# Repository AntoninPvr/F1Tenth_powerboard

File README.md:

# F1Tenth power board

This repository contains the power board design for a F1Tenth car.

Designed on Kicad 9.0.6.

## History
This project was originally launched in the summer of 2024 at [CTU](https://www.cvut.cz/en), thanks to David Zahrádka, to facilitate easier experimentation for researchers.

## Assembled PCB

## Features

This board is designed to power all F1tenth components. Two 3S Li-Po batteries power the board. Those batteries are connected in parallel throught an ORing circuitry. This allow to hot swap batteries. The output of the ORing is named `BATT_SYS` and is directly connected to VESC output **without protections**.

The `Jetson` terminals is also connected to `BATT_SYS` but protected by a dedicated 5A e-fuse. The `P_0` and `P_1` terminals are connected to `BATT_SYS` through another e-fuse and can draw up to 5A.

A 5V 6A buck converter provide power to the `USB A` connector. This output is protected for overcurrent up to 6A.

## SAFETY WARNING

Li-Po can provide **huge amount** of current. **Be careful** when handling the board. **Do not short circuit** the batteries and VESC output as they are not protected. Do not exceed the maximum input voltage: **20V**.

PCB can be hot when drawing high current. 

## Absolute maximum ratings
| | Min | Max | Unit
--- | --- | --- | ---
Battery voltage | 6 | 20 | V
Jetson current |  | 5 | A
P0 + P1 current |  | 5 | A
USB current |  | 6 | A
VESC current |  | 60 | A

## File structure

- [power_board.pro](power_board_f1tenth.kicad_pro) - Kicad project file
- [power_board.sch](power_board_f1tenth.kicad_sch) - Schematic
- [power_board.kicad_pcb](power_board_f1tenth.kicad_pcb) - PCB layout
- [symbol/](symbol/) - Custom symbols
- [power_board.pretty/](symbol/) - Custom footprints

## DRC

Design rules checks comply with JLCPCB capabilities.

## Circuit

### Ideal diode

Ideal diode behavior is achieved by LM74700 and the high power N channel MOSFET IAUCN04S7L005.

The `J3` can be used to connect a battery life indicator.

Circuit for battery B is identical.

### Buck converter

Provide 5V 6A to the USB connector. Data p and n are tied together as the USB connector is only used for power, it helps to trigger high current mode on some device.

TPS51386 also provide overcurrent protection, under and overvoltage protection.

### E-fuse

Those e-fuse are used to protect the Jetson and the peripherals. The TPS25980 is configured to limit the current to 5A. It allow overcurrrent for 2ms to allow inrush current. Number of retry is unlimited and rise time is 1ms.

### Terminals

Terminal are bornier-2_P5.08mm. They are used to connect the peripherals and the Jetson. They are from the MSTB series from Phoenix Contact. They can be easily unpluged and pluged.

## PCB

## BOM
Designator | Footprint | Quantity | Value
--- | --- | --- | ---
C1, C14, C15, C18, C2, C5, C6, C7, C8 | 0805 | 9 | 22u
C10 | 0805 | 1 | 22p
C11 | 0805 | 1 | NC
C12, C13, C16, C21, C3, C4 | 0805 | 6 | 100n
C17, C19, C20, C22, C23, C24 | 0805 | 6 | 10n
C9 | 0805 | 1 | 1u
D1 | SOT96P237X111-3N | 1 | 3.3v
D2, D3, D4, D5 | 0805 | 4 | LED
J1 | USB_A_Molex_67643_Horizontal | 1 | USB_A
J7 | TerminalBlock_bornier-2_P5.08mm | 1 | P0
J8 | TerminalBlock_bornier-2_P5.08mm | 1 | P1
J9 | TerminalBlock_bornier-2_P5.08mm | 1 | JETSON
L1 | SRP12701R5M | 1 | 1u5
Q1, Q2 | IAUCN04S7L005 | 2 | IAUCN04S7L005
R1, R13, R2, R4, R8 | 0805 | 5 | 150k
R10, R11, R5, R6 | 0805 | 4 | 1k
R12, R7 | 0805 | 2 | 620k
R14, R9 | 0805 | 2 | 300
R3 | 0805 | 1 | 20k
U1 | RJN_Package_12-Pin_VQFN-HR | 1 | TPS51386
U2, U3 | SOT65P280X110-8N | 2 | LM74700QDDF*
U4, U5 | TPS259803ONRGER | 2 | TPS259803ONRGER

Warning: *LM74700 exist in different packages. The one used in this design is the 8 pin LM74700D.

## Prices *(Updated on August 18, 2024)*

Example prices on Mouser and JLCPCB.

Shipping is not included.

JLCPCB prices for 5 boards: 1,83 € = 46CZK

Mouser price for 1 board: 28,53 € = 723CZK

Total: **30,36 € = 769CZK** 

*This board costs half the price of the original [F1tenth power board](https://f1tenth.readthedocs.io/en/foxy_test/getting_started/build_car/bom.html)...*

| ID Mouser | ID de fab. | Fabricant | ID client | Description | Qté. | Prix (EUR) | Ext. : (EUR) |
| --- | --- | --- | --- | --- | --- | --- | --- |
| 595-TPS51386RJNR | TPS51386RJNR | Texas Instruments | | 4.5-V to 24-V input, 8-A synchronous buck converter 12-VQFN-HR -40 to 125 | 1 | 0,967 € | 0,97 € |
| 726-IAUCN04S7L005ATM | IAUCN04S7L005ATMA1 | Infineon | | MOSFET N | 2 | 2,48 € | 4,96 € |
| 595-LM74700QDDFRQ1 | LM74700QDDFRQ1 | Texas Instruments | | 3.2-V to 65-V, 80-uA IQ automotive ideal diode controller 8-SOT-23-THIN -40 to 125 | 2 | 1,66 € | 3,32 € |
| 187-CL21A226MAYNNNE | CL21A226MAYNNNE | Samsung Electro-Mechanics | | MLCC - CMS 22uF+/-20% 25V X5R 2 0805 | 10 | 0,106 € | 1,06 € |
| 71-CRCW0805J-20K-E3 | CRCW080520K0JNEA | Vishay | | CMS 1/8watt 20Kohms 5% 200ppm | 10 | 0,02 € | 0,20 € |
| 187-CL21B104KBFNNNE | CL21B104KBFNNNE | Samsung Electro-Mechanics | | MLCC - CMS 100n SAMSUNG | 10 | 0,019 € | 0,19 € |
| 187-CL21B105MBFNNNE | CL21B105MBFNNNE | Samsung Electro-Mechanics | | MLCC - CMS X7R, 1uF, +/-20%, 50v, 0805 | 10 | 0,025 € | 0,25 € |
| 863-BZX84C3V9LT1G | BZX84C3V9LT1G | onsemi | | Zener 3.9V 250mW | 1 | 0,093 € | 0,09 € |
| 652-SRP1270-1R5M | SRP1270-1R5M | Bourns | | CMS 1.5uH 20% SMD 1270 | 1 | 0,911 € | 0,91 € |
| 640-USB1130-15-A | USB1130-15-A | Global Connector Technology (GCT) | | USB A 2.0 Skt RA High Life 15u" T Hole W/Shell Stake T & R | 1 | 0,735 € | 0,74 € |
| 595-TPS259803ONRGER | TPS259803ONRGER | Texas Instruments | | Hotswap controller 2.7-V to 24-V, 8-A, 3-mohm smart eFuse 24-VQFN -40 to 125 | 2 | 1,43 € | 2,86 € |
| 77-VJ0805A220JXACBC | VJ0805A220JXACW1BC | Vishay | | MLCC - CMS 0805 22pF 50volts C0G 5% | 10 | 0,052 € | 0,52 € |
| 71-CRCW0805-150K-E3 | CRCW0805150KFKEA | Vishay | | CMS 1/8watt 150Kohms 1% 100ppm | 10 | 0,023 € | 0,23 € |
| 187-CL21C103JBFNNNE | CL21C103JBFNNNE | Samsung Electro-Mechanics | |  MLCC - CMS 10nF+/-5% 50V C0G 20 0805 | 10 | 0,105 € | 1,05 € |
| 71-CRCW0805620KFKEA | CRCW0805620KFKEA | Vishay | | CMS 1/8watt 620Kohms 1% | 10 | 0,031 € | 0,31 € |
| 71-CRCW0805300RFKEA | CRCW0805300RFKEA | Vishay | | CMS 1/8watt 300ohms 1% | 10 | 0,023 € | 0,23 € |
| 71-CRCW08051K00JNEAC | CRCW08051K00JNEAC | Vishay | | CMS 1/8Watt 1Kohms 5% Commercial Use | 10 | 0,019 € | 0,19 € |
| 710-150080VS75000 | 150080VS75000 | Wurth Elektronik | | LED CMS WL-SMCW SMDMono TpVw Waterclr 0805 BrtGrn | 5 | 0,177 € | 0,89 € |
| 651-1752492 | 1752492 | Phoenix Contact | | Female bornier MSTBA 2,5 HC/ 2-GU | 3 | 0,465 € | 1,40 € |
| 651-1892398 | 1892398 | Phoenix Contact | | Male bornier MSTB 2,5/ 2-ST- 5,08 BD:NZ KEG | 6 | 1,36 € | 8,16 € |

## Additionals notes

- Copper thickness:
    2oz is recommended as batteries can provide high current. But 1oz can be sufficient for the F1tenth car, as it is not used at full power.

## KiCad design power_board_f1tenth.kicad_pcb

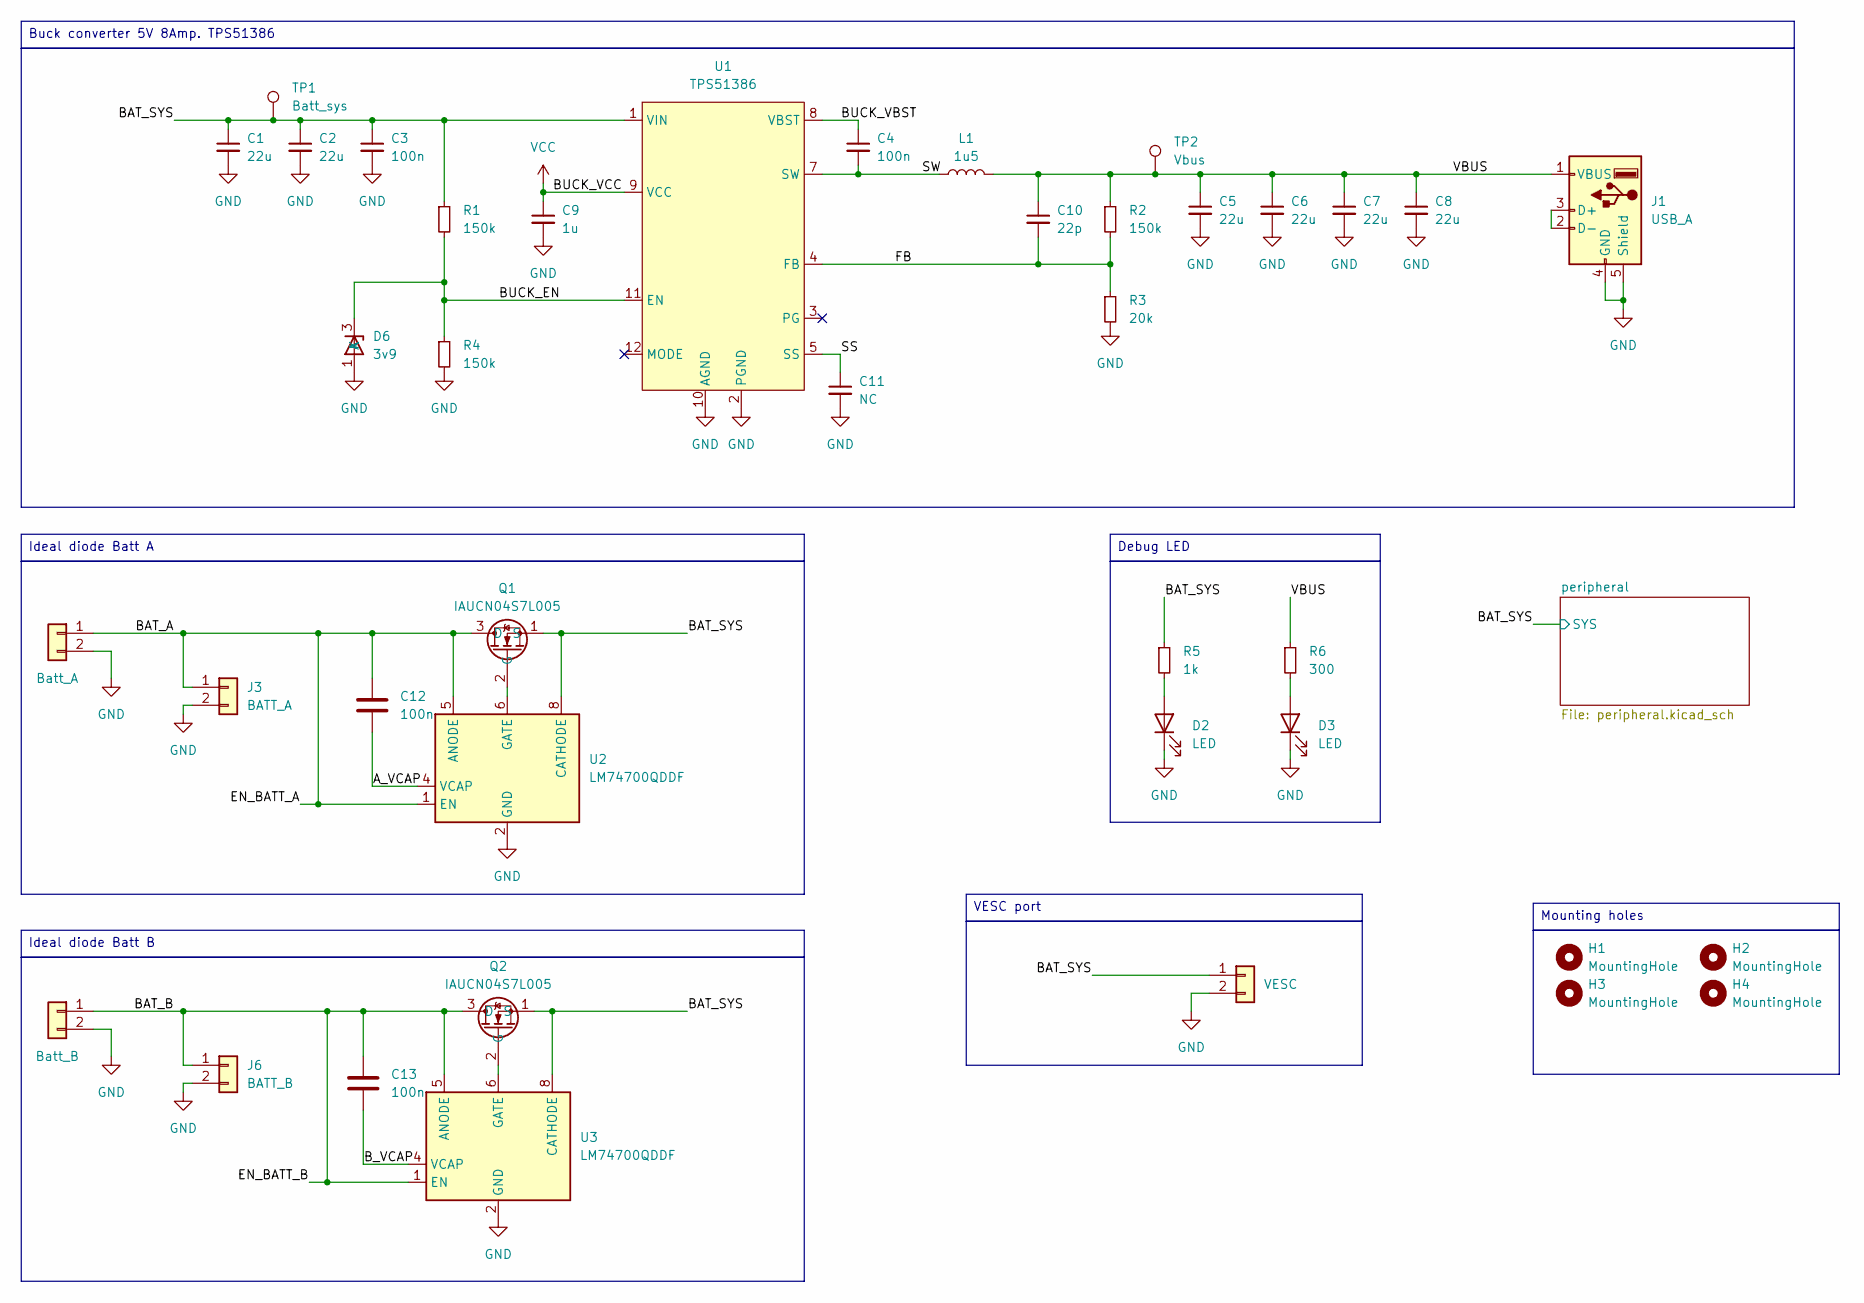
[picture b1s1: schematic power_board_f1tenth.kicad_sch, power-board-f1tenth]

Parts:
C1, C2, C5, C6, C7, C8: 22u; C_0805_2012Metric
C3, C4, C12, C13: 100n; C_0805_2012Metric
C9: 1u; C_0805_2012Metric
C10: 22p; C_0805_2012Metric
C11: NC; C_0805_2012Metric
D2, D3: LED; LED_0805_2012Metric
D6: 3v9; SOT-23-3
H1, H2, H3, H4: MountingHole; MountingHole_5.3mm_M5_DIN965
J1: USB_A; USB_A_Molex_67643_Horizontal
J2: Batt_A; Battery_pad
J3: BATT_A; PinHeader_1x02_P2.54mm_Vertical
J4: VESC; Battery_pad
J5: Batt_B; Battery_pad
J6: BATT_B; PinHeader_1x02_P2.54mm_Vertical
L1: 1u5; SRP12701R5M
Q1, Q2: IAUCN04S7L005
R1, R2, R4: 150k; R_0805_2012Metric
R3: 20k; R_0805_2012Metric
R5: 1k; R_0805_2012Metric
R6: 300; R_0805_2012Metric
TP1: Batt_sys; TestPoint_Pad_D1.0mm
TP2: Vbus; TestPoint_Pad_D1.0mm
U1: TPS51386; RJN_Package_12-Pin_VQFN-HR
U2, U3: LM74700QDDF; SOT65P280X110-8N

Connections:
/A_VCAP: C12.2, U2.4 (VCAP)
/BAT_A: C12.1, J2.1, J3.1, Q1.3 (D), U2.1 (EN), U2.5 (ANODE)
/BAT_B: C13.1, J5.1, J6.1, Q2.3 (D), U3.1 (EN), U3.5 (ANODE)
/BAT_SYS: C1.1, C2.1, C3.1, J4.1, Q1.1 (S), Q2.1 (S), R1.1, R5.1, TP1.1, U1.1 (VIN), U2.8 (CATHODE), U3.8 (CATHODE); also elsewhere on the board
/BUCK_EN: D6.3 (K), R1.2, R4.1, U1.11 (EN)
/BUCK_VBST: C4.1, U1.8 (VBST)
/B_VCAP: C13.2, U3.4 (VCAP)
/FB: C10.2, R2.2, R3.1, U1.4 (FB)
/SS: C11.1, U1.5 (SS)
/SW: C4.2, L1.1, U1.7 (SW)
/VBUS: C5.1, C6.1, C7.1, C8.1, C10.1, J1.1 (VBUS), L1.2, R2.1, R6.1, TP2.1
GND: C1.2, C2.2, C3.2, C5.2, C6.2, C7.2, C8.2, C9.2, C11.2, D2.1 (K), D3.1 (K), D6.1 (A), J1.4 (GND), J1.5 (Shield), J2.2, J3.2, J4.2, J5.2, J6.2, R3.2, R4.2, U1.2 (PGND), U1.10 (AGND), U2.2 (GND), U3.2 (GND); also elsewhere on the board
unnamed: D2.2 (A), R5.2
unnamed: D3.2 (A), R6.2
unnamed: J1.2 (D-), J1.3 (D+)
unnamed: Q1.2 (G), U2.6 (GATE)
unnamed: Q2.2 (G), U3.6 (GATE)
VCC: C9.1, U1.9 (VCC)

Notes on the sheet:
Debug LED
Ideal diode Batt B
Mounting holes
Buck converter 5V 8Amp. TPS51386
VESC port
Ideal diode Batt A

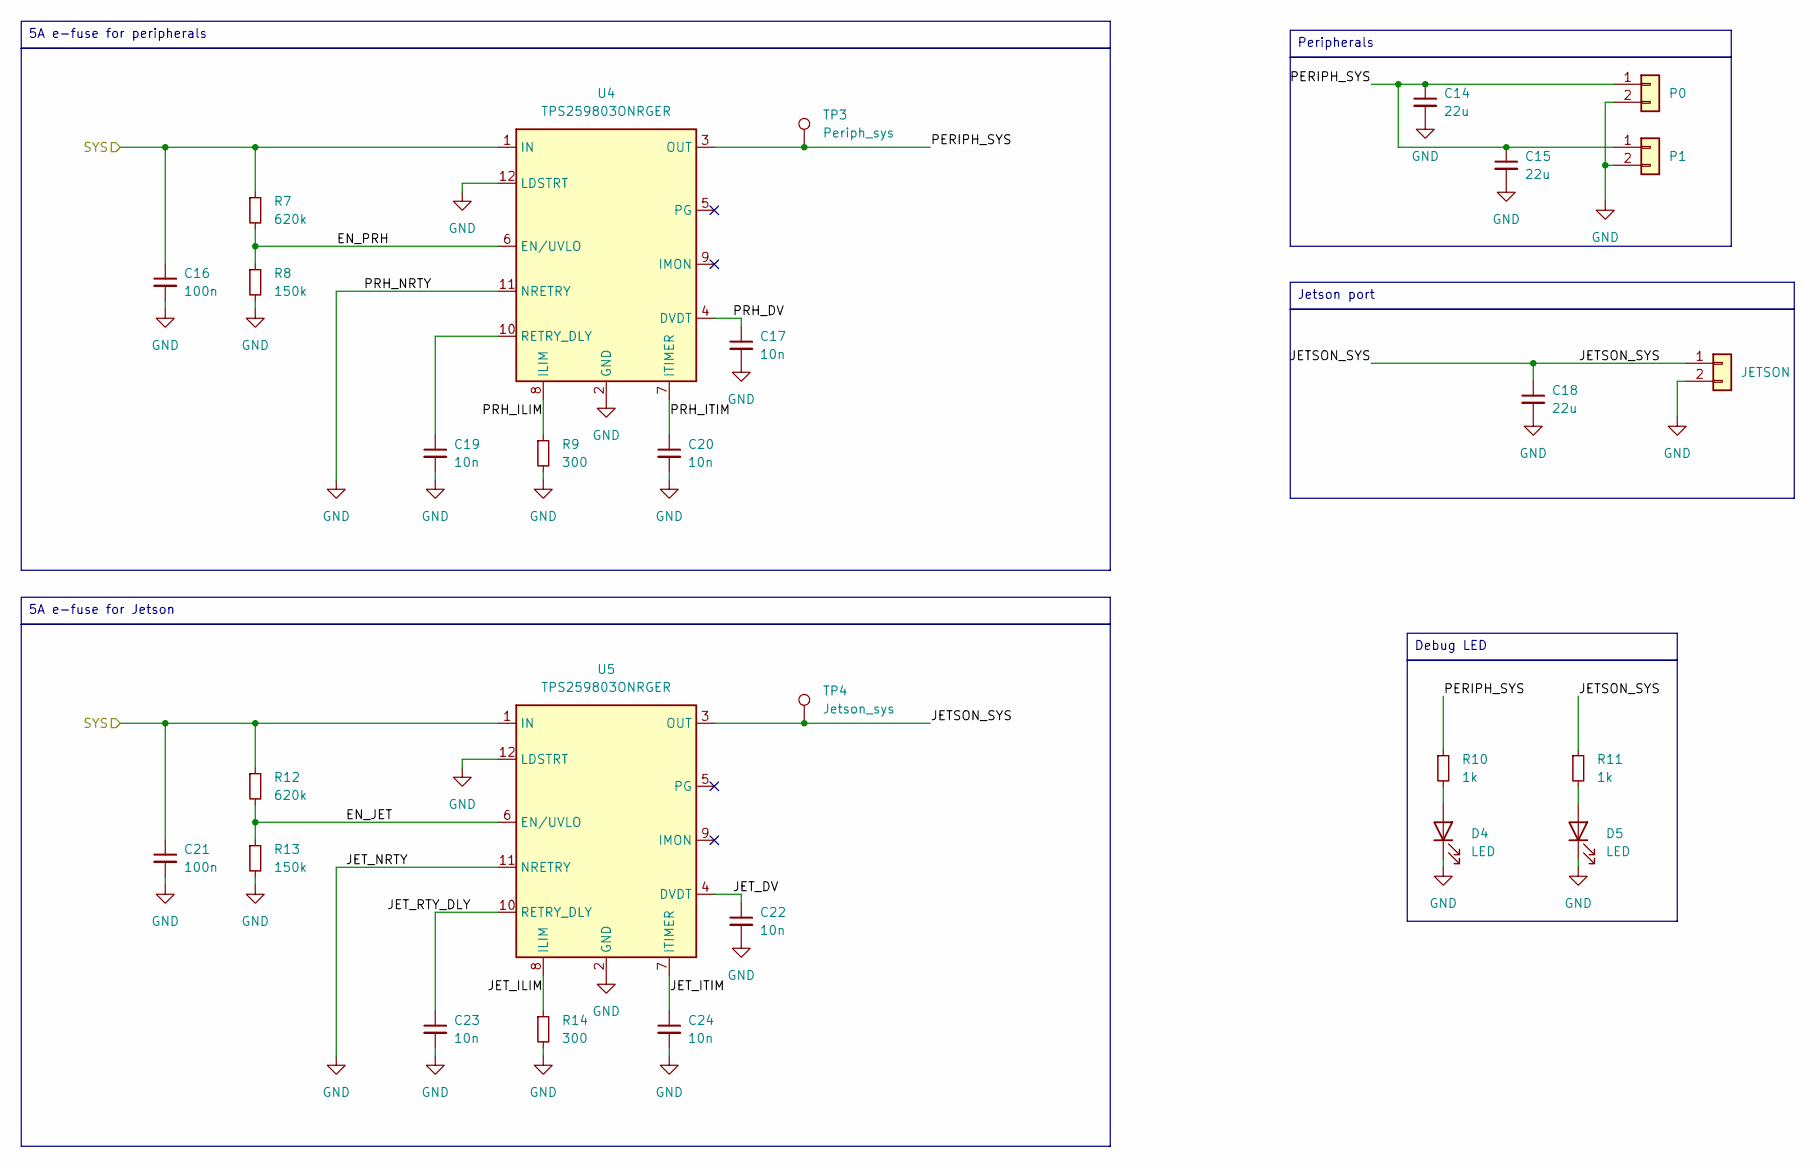
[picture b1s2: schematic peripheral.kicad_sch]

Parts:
C14, C15, C18: 22u; C_0805_2012Metric
C16, C21: 100n; C_0805_2012Metric
C17, C19, C20, C22, C23, C24: 10n; C_0805_2012Metric
D4, D5: LED; LED_0805_2012Metric
J7: P0; TerminalBlock_bornier-2_P5.08mm
J8: P1; TerminalBlock_bornier-2_P5.08mm
J9: JETSON; TerminalBlock_bornier-2_P5.08mm
R7, R12: 620k; R_0805_2012Metric
R8, R13: 150k; R_0805_2012Metric
R9, R14: 300; R_0805_2012Metric
R10, R11: 1k; R_0805_2012Metric
TP3: Periph_sys; TestPoint_Pad_D1.0mm
TP4: Jetson_sys; TestPoint_Pad_D1.0mm
U4, U5: TPS259803ONRGER; Mouser Part Number 595-TPS259803ONRGER

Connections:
/BAT_SYS: C16.1, C21.1, R7.1, R12.1, U4.1 (IN), U5.1 (IN); also elsewhere on the board
/peripheral/EN_JET: R12.2, R13.1, U5.6 (EN/UVLO)
/peripheral/EN_PRH: R7.2, R8.1, U4.6 (EN/UVLO)
/peripheral/JETSON_SYS: C18.1, J9.1, R11.1, TP4.1, U5.3 (OUT)
/peripheral/JET_DV: C22.1, U5.4 (DVDT)
/peripheral/JET_ILIM: R14.1, U5.8 (ILIM)
/peripheral/JET_ITIM: C24.1, U5.7 (ITIMER)
/peripheral/JET_RTY_DLY: C23.1, U5.10 (RETRY_DLY)
/peripheral/PERIPH_SYS: C14.1, C15.1, J7.1, J8.1, R10.1, TP3.1, U4.3 (OUT)
/peripheral/PRH_DV: C17.1, U4.4 (DVDT)
/peripheral/PRH_ILIM: R9.1, U4.8 (ILIM)
/peripheral/PRH_ITIM: C20.1, U4.7 (ITIMER)
GND: C14.2, C15.2, C16.2, C17.2, C18.2, C19.2, C20.2, C21.2, C22.2, C23.2, C24.2, D4.1 (K), D5.1 (K), J7.2, J8.2, J9.2, R8.2, R9.2, R13.2, R14.2, U4.2 (GND), U4.11 (NRETRY), U4.12 (LDSTRT), U5.2 (GND), U5.11 (NRETRY), U5.12 (LDSTRT); also elsewhere on the board
unnamed: D4.2 (A), R10.2
unnamed: D5.2 (A), R11.2
unnamed: C19.1, U4.10 (RETRY_DLY)

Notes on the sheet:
5A e-fuse for Jetson
5A e-fuse for peripherals
Peripherals
Debug LED
Jetson port

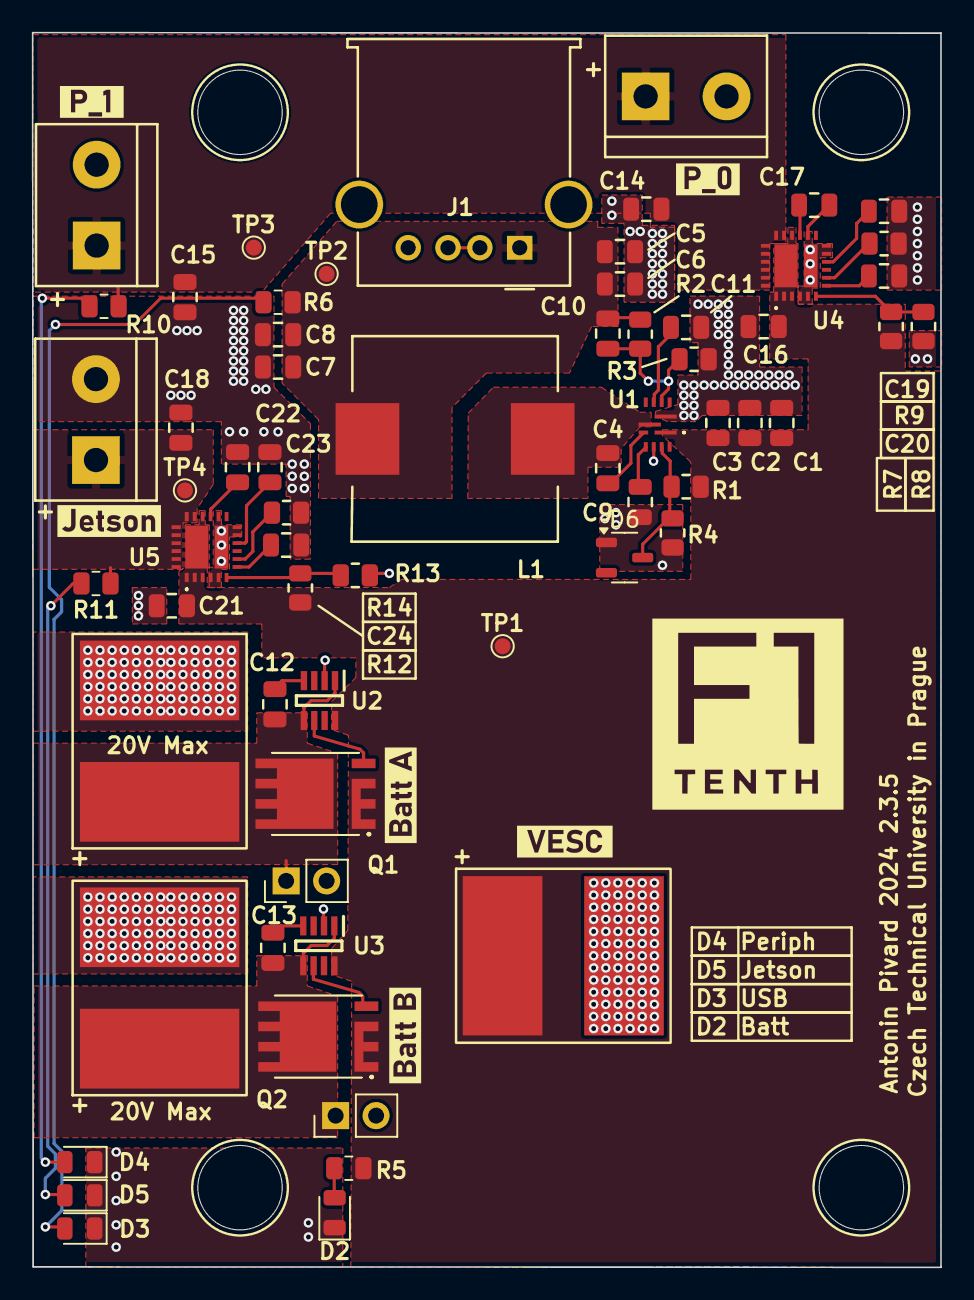
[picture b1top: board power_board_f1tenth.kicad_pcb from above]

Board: 2 copper layers, 57.0 x 77.5 mm, 68 parts (0 on the bottom side), 32 nets.

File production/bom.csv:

Designator,Footprint,Quantity,Value,LCSC Part #
"C1, C14, C15, C18, C2, C5, C6, C7, C8",0805,9,22u,
C10,0805,1,22p,
C11,0805,1,NC,
"C12, C13, C16, C21, C3, C4",0805,6,100n,
"C17, C19, C20, C22, C23, C24",0805,6,10n,
C9,0805,1,1u,
"D2, D3, D4, D5",0805,4,LED,
D6,SOT-23-3,1,3v9,
J1,USB_A_Molex_67643_Horizontal,1,USB_A,
J2,Battery_pad,1,Batt_A,
J3,PinHeader_1x02_P2.54mm_Vertical,1,BATT_A,
J4,Battery_pad,1,VESC,
J5,Battery_pad,1,Batt_B,
J6,PinHeader_1x02_P2.54mm_Vertical,1,BATT_B,
J7,TerminalBlock_bornier-2_P5.08mm,1,P0,
J8,TerminalBlock_bornier-2_P5.08mm,1,P1,
J9,TerminalBlock_bornier-2_P5.08mm,1,JETSON,
L1,SRP12701R5M,1,1u5,
"Q1, Q2",IAUCN04S7L005,2,IAUCN04S7L005,
"R1, R13, R2, R4, R8",0805,5,150k,
"R10, R11, R5",0805,3,1k,
"R12, R7",0805,2,620k,
"R14, R6, R9",0805,3,300,
R3,0805,1,20k,
TP1,TestPoint_Pad_D1.0mm,1,Batt_sys,
TP2,TestPoint_Pad_D1.0mm,1,Vbus,
TP3,TestPoint_Pad_D1.0mm,1,Periph_sys,
TP4,TestPoint_Pad_D1.0mm,1,Jetson_sys,
U1,RJN_Package_12-Pin_VQFN-HR,1,TPS51386,
"U2, U3",SOT65P280X110-8N,2,LM74700QDDF,
"U4, U5",TPS259803ONRGER,2,TPS259803ONRGER,

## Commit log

2024-08-12 Migrate from CTU private repo to personal repo
2025-11-09 added .gitignore
2025-11-09 Added history section on readme
2025-11-09 Updated to Kicad 9.0
2025-11-09 added assembled pcb pictures
